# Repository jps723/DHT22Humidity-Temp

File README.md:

# DHT22 Humidity/Temp Module Build Notes 3/3/20

This project is in partnership with [Bantam Tools](https://www.bantamtools.com)

**Design Notes:**

This module features the [DHT22 humidity/temperature sensor](https://www.sparkfun.com/datasheets/Sensors/Temperature/DHT22.pdf), also referred to as the AM2302. The pinout is as follows:

On the module, the DHT22 is intended to rest perpendicular to the board.  There is a 4.7k pull-up resistor on the data line, a .1uF filtering capacitor on the VCC line, and a power indicating LED via 1k resistor. The module uses 90 degree male headers allowing for easy breadboarding.  

# Build Process
It’s easiest to solder in this order:
```
1. SMD components
2. Male headers
3. LED
4. DHT22 (bend legs before soldering)
```
**Mill Time**
	Bits: 1/32” & 1/64”: < 3mins
	Or
	1/64” Alone: 8mins

**Test**
```
1. Install the Adafruit DHT Sensor library
2. Examples > DHT Sensor Library > DHTtester
3. Connect 5v to pin1 on the module, connect D2 (Default in example code) to pin2 on the module, and GND to pin3
4. DHT22 is the default type set in the example sketch.  Change this in the code if using a different DHTxx sensor.   
5. Upload code
6.  Open Serial Monitor
```

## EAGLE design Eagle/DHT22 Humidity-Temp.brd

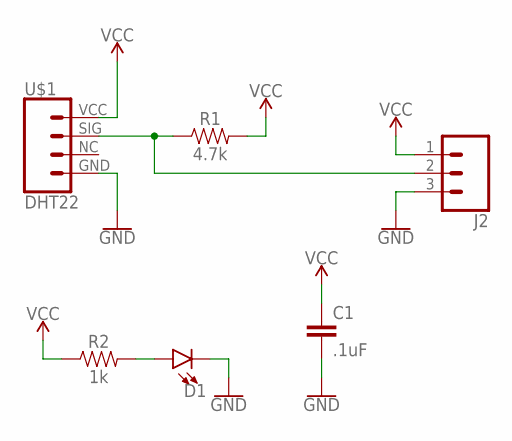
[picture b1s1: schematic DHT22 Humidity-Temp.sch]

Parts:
C1: .1uF; 0805
D1: LED-3MM-NO_SILK; LED_3MM-NS
J2: CONN_03LONGPADS; 1X03_LONGPADS
R1: 4.7k; 0805
R2: 1k; 0805
U$1: DHT22

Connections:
GND: C1.2, D1.K (C), J2.3, U$1.GND (1)
unnamed: D1.A, R2.2
SIGNAL: J2.2, R1.1, U$1.SIG (3)
VCC: C1.1, J2.1, R1.2, R2.1, U$1.VCC (4)

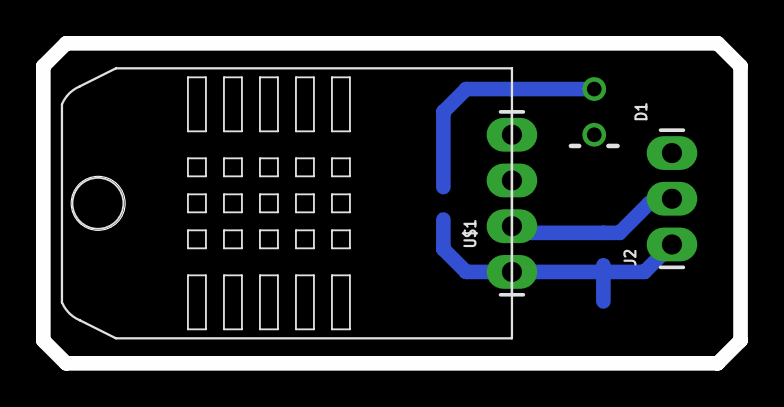
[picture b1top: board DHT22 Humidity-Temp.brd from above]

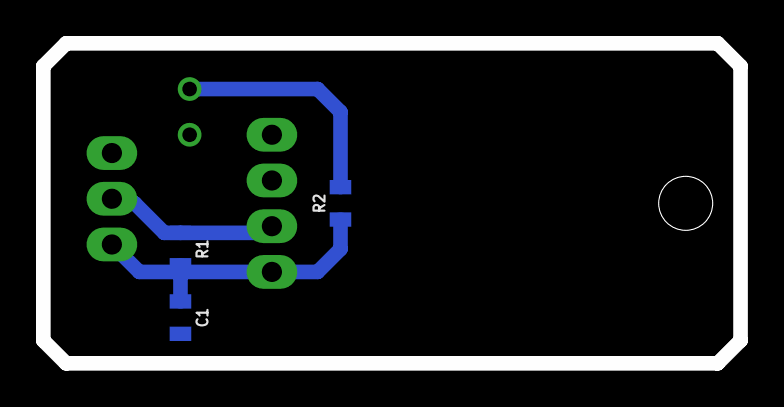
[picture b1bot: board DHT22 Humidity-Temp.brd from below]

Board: 2 copper layers, 38.7 x 17.8 mm, 6 parts (3 on the bottom side), 4 nets.

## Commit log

2020-10-30 added bantam tools credit

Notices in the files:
parts and their libraries:
SparkFun-Connectors: Licensing: Creative Commons ShareAlike 4.0 International - https://creativecommons.org/licenses/by-sa/4.0
